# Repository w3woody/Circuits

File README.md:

# Circuits

This repository contains the [Eagle](https://www.autodesk.com/products/eagle/free-download) files and [iCircuit](https://icircuitapp.com) files for the various circuits designed on [The Hacking Den](https://hackingden.com).

Note that many of the circuits are designed to fit on a two-layer board and fit in a 100mm x 100mm board--which fits within the specifications for inexpensive circuit board manufacturing by [Seeed Studio](https://www.seeedstudio.com/fusion_pcb.html).

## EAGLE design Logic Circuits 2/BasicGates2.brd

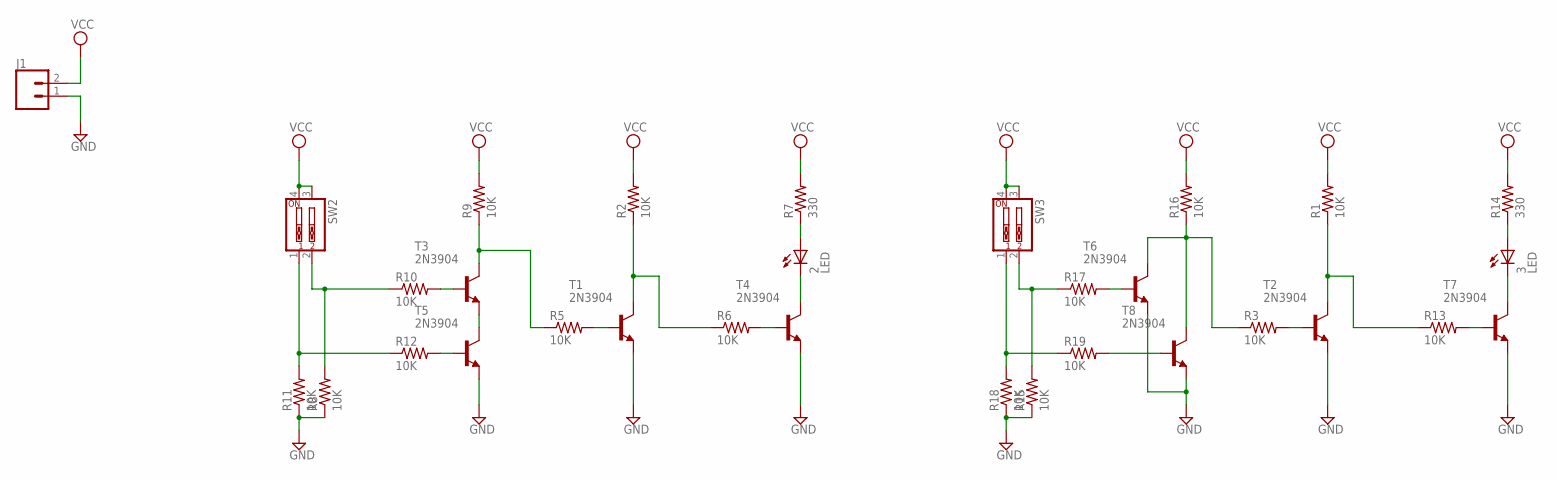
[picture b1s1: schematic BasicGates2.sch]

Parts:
2, 3: LED; LED5MM
J1: CONN_02; 1X02
R1, R2, R3, R5, R6, R8, R9, R10, R11, R12, R13, R15, R16, R17, R18, R19: 10K; 0309/10
R7, R14: 330; 0309/10
SW2, SW3: SW_DIP-2; EDG-02
T1, T2, T3, T4, T5, T6, T7, T8: 2N3904; TO92

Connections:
GND: J1.1, R8.1, R11.1, R15.1, R18.1, T1.3 (E), T2.3 (E), T4.3 (E), T5.3 (E), T6.3 (E), T7.3 (E), T8.3 (E)
unnamed: R2.1, R6.1, T1.1 (C)
unnamed: R5.2, T1.2 (B)
unnamed: R1.1, R13.1, T2.1 (C)
unnamed: R6.2, T4.2 (B)
unnamed: 2.A, R7.1
unnamed: 2.K (C), T4.1 (C)
unnamed: R5.1, R9.1, T3.1 (C)
unnamed: R10.2, T3.2 (B)
unnamed: R8.2, R10.1, SW2.2
unnamed: T3.3 (E), T5.1 (C)
unnamed: R12.2, T5.2 (B)
unnamed: R11.2, R12.1, SW2.1
unnamed: R13.2, T7.2 (B)
unnamed: 3.A, R14.1
unnamed: 3.K (C), T7.1 (C)
unnamed: R3.1, R16.1, T6.1 (C), T8.1 (C)
unnamed: R17.2, T6.2 (B)
unnamed: R15.2, R17.1, SW3.2
unnamed: R3.2, T2.2 (B)
unnamed: R19.2, T8.2 (B)
unnamed: R18.2, R19.1, SW3.1
VCC: J1.2, R1.2, R2.2, R7.2, R9.2, R14.2, R16.2, SW2.3, SW2.4, SW3.3, SW3.4

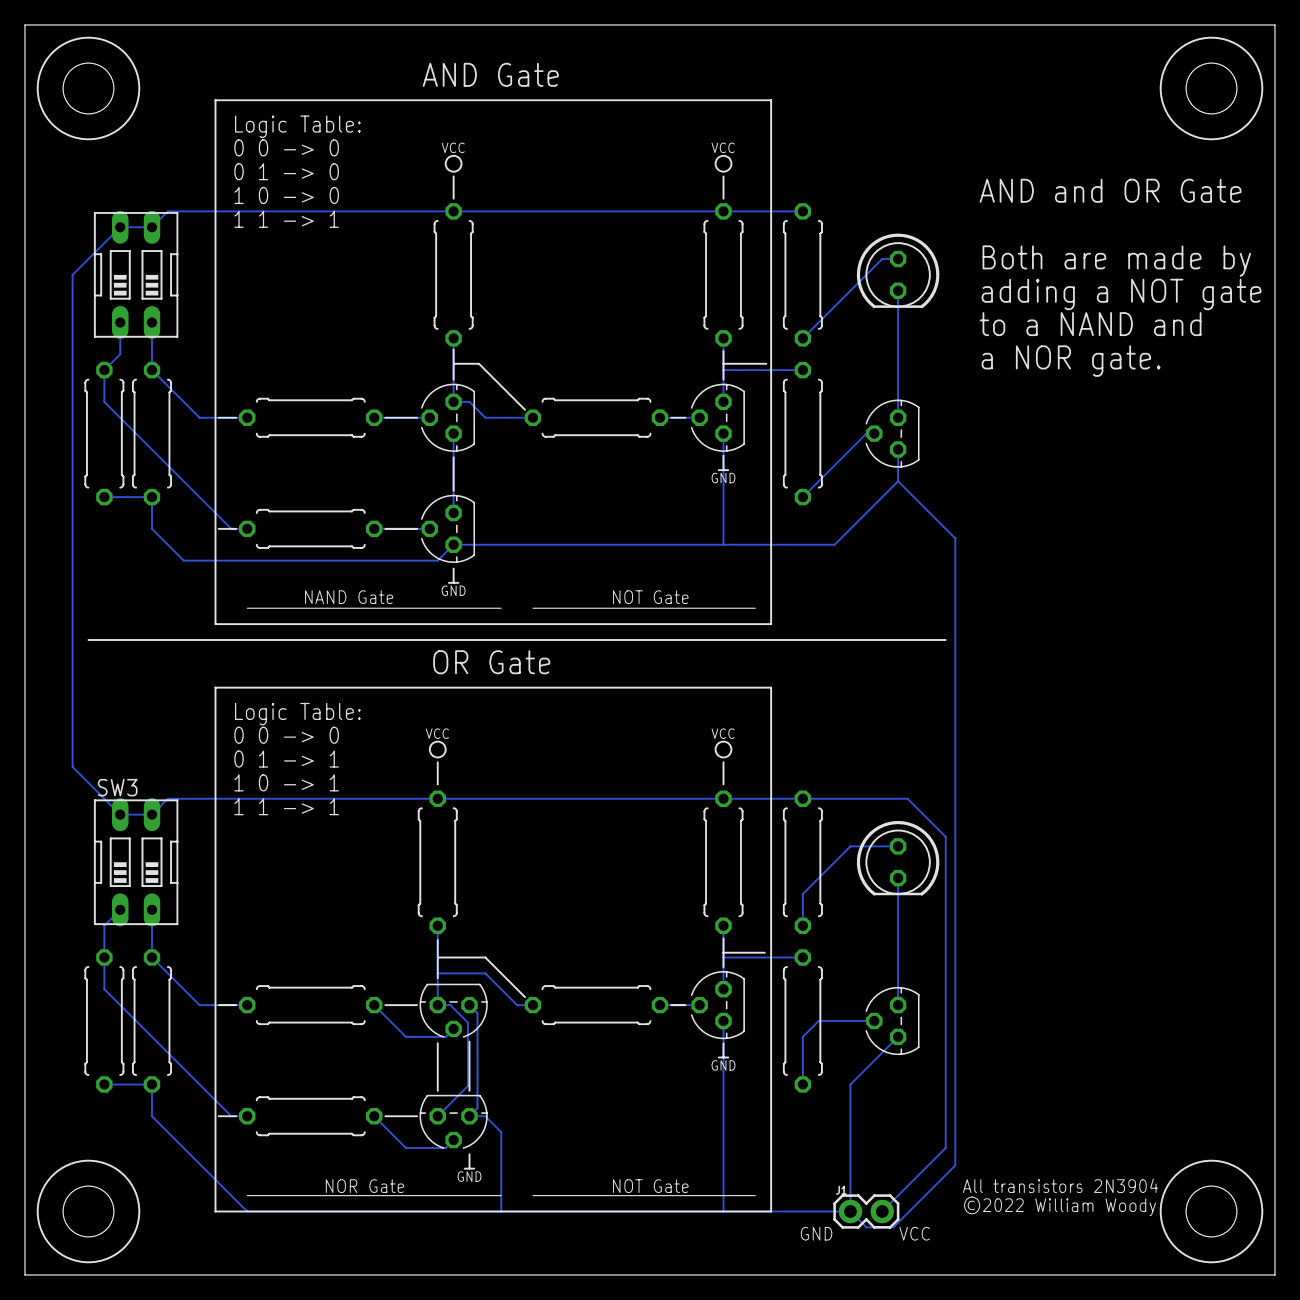
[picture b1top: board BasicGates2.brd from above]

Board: 2 copper layers, 100.0 x 100.0 mm, 31 parts (0 on the bottom side), 23 nets.

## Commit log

2022-12-27 Add Circuits 1
2022-12-27 Update board. Upload AND/OR

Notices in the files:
Logic Circuits 2/BasicGates2.brd:
©2022 William Woody
parts and their libraries:
SparkFun-Connectors: Licensing: Creative Commons ShareAlike 4.0 International - https://creativecommons.org/licenses/by-sa/4.0
